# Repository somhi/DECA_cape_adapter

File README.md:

# DECA cape adapter

Working in a DECA cape adapter from [DECA retro cape 2](https://github.com/somhi/DECA_retro_cape_2) to a DE10-Lite FPGA board.

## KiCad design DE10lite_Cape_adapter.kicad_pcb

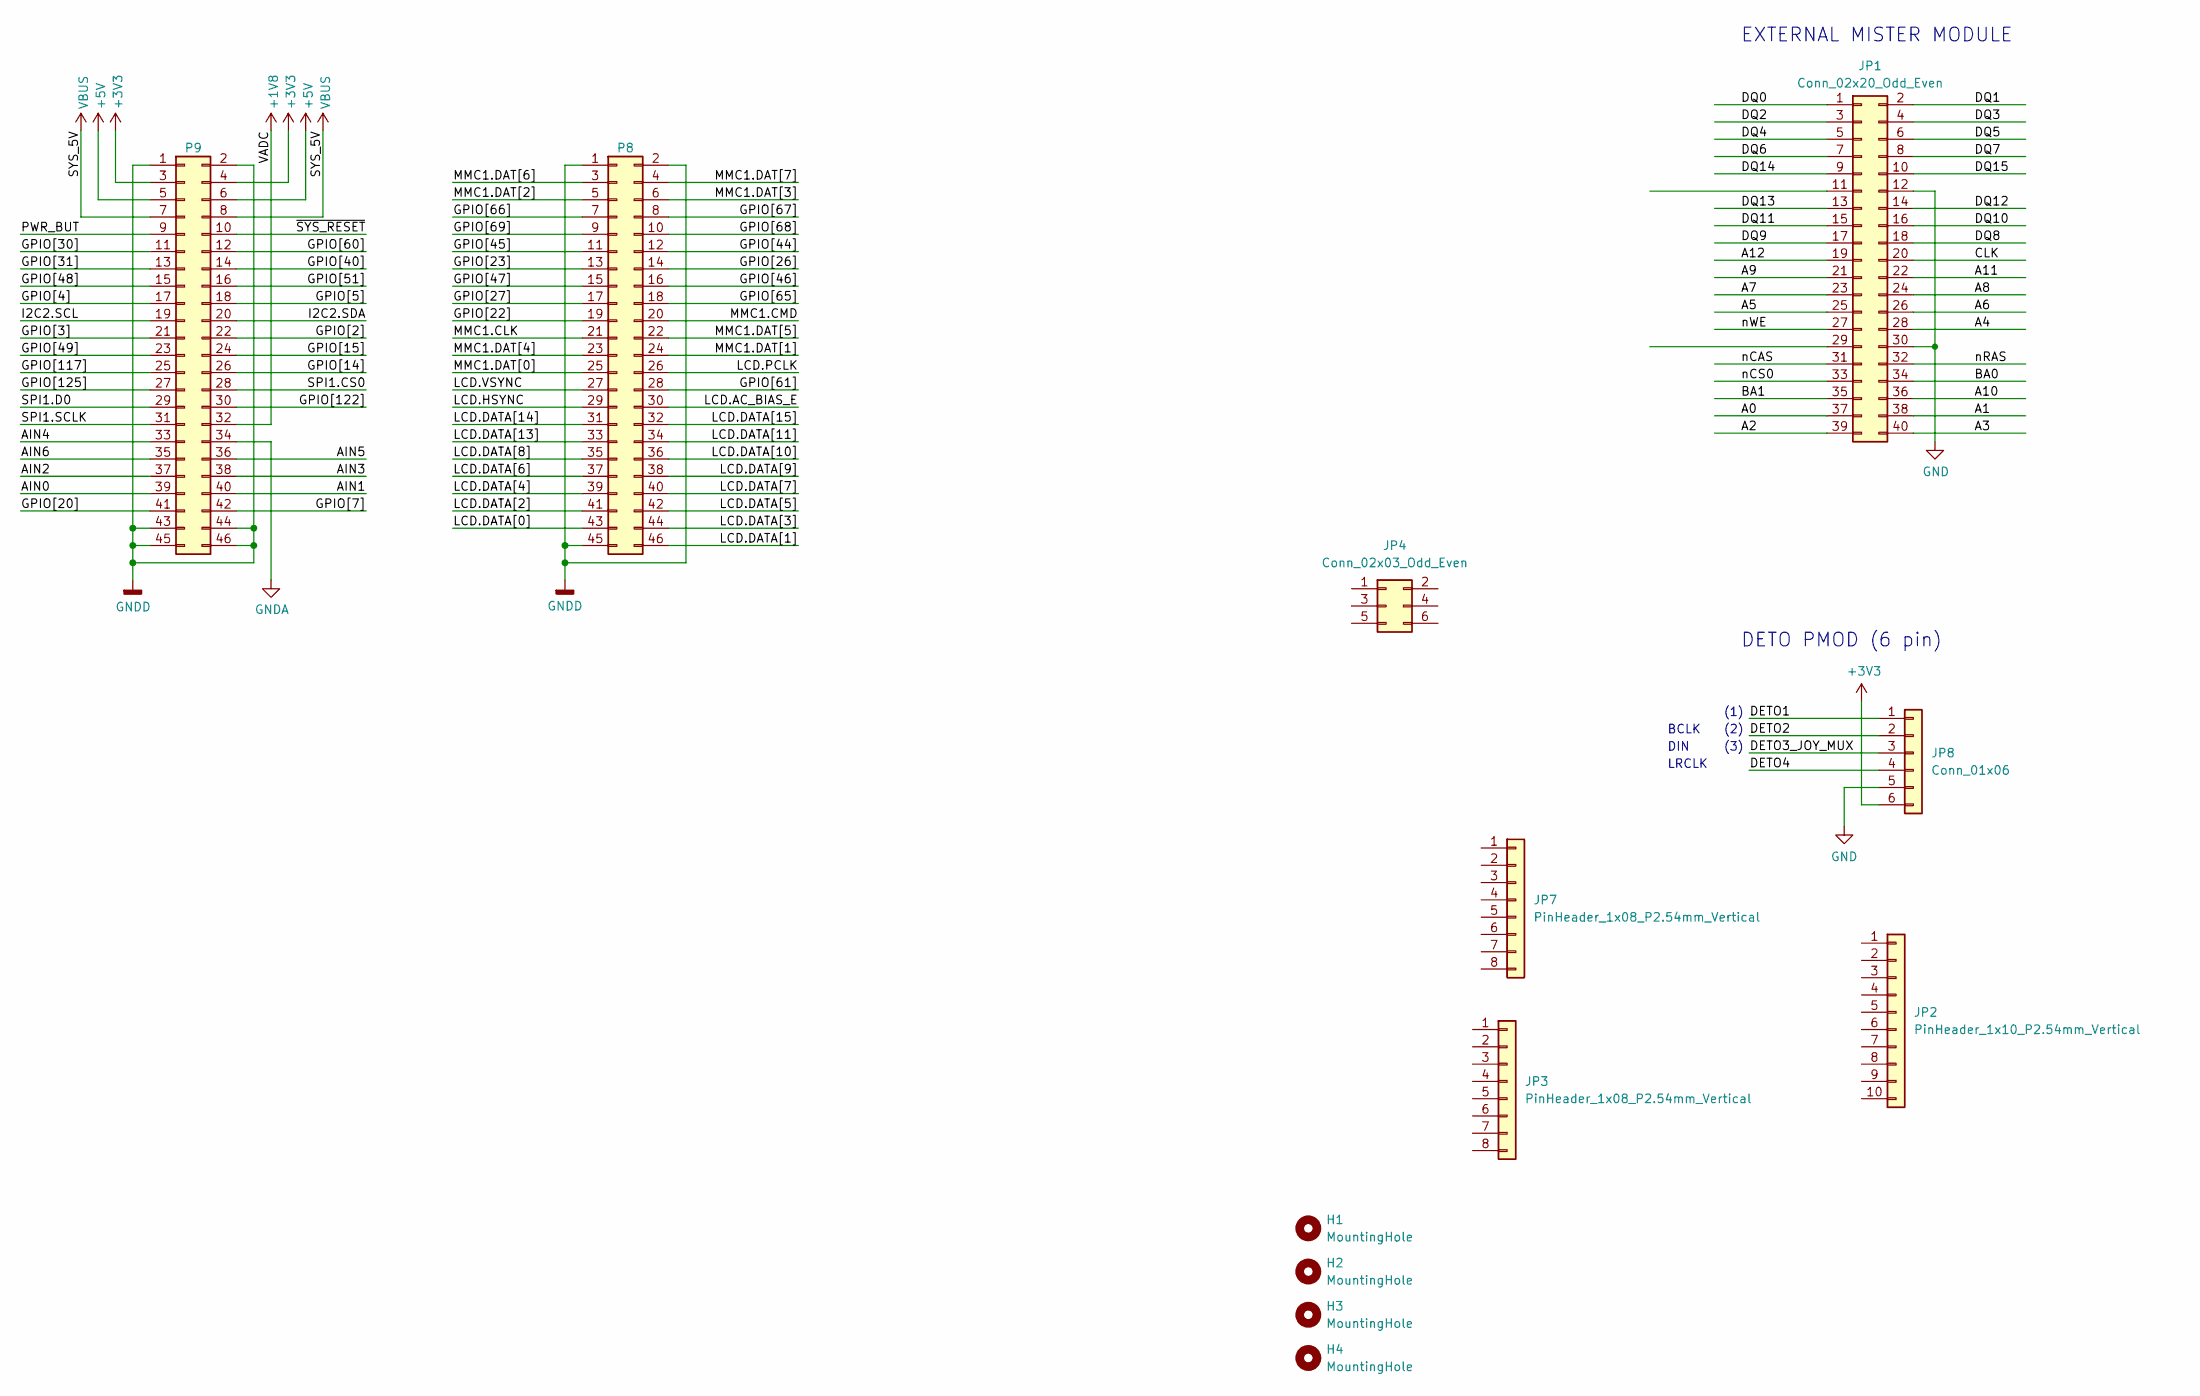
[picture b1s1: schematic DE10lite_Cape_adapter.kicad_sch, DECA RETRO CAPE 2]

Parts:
H1, H2, H3, H4: MountingHole; MountingHole_3mm
JP1: Conn_02x20_Odd_Even; PinSocket_2x20_P2.54mm_Vertical
JP2: PinHeader_1x10_P2.54mm_Vertical
JP3, JP7: PinHeader_1x08_P2.54mm_Vertical
JP4: Conn_02x03_Odd_Even; PinSocket_2x03_P2.54mm_Vertical
JP8: Conn_01x06; PinHeader_1x06_P2.54mm_Vertical
P8, P9: BeagleBone_Black_Header; PinHeader_2x23_P2.54mm_Vertical

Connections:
+1V8: P9.32
+3V3: JP8.6, P9.3, P9.4
+5V: P9.5, P9.6
/A0: JP1.37
/A1: JP1.38
/A2: JP1.39
/A3: JP1.40
/A4: JP1.28
/A5: JP1.25
/A6: JP1.26
/A7: JP1.23
/A8: JP1.24
/A9: JP1.21
/A10: JP1.36
/A11: JP1.22
/A12: JP1.19
/AIN0: P9.39
/AIN1: P9.40
/AIN2: P9.37
/AIN3: P9.38
/AIN4: P9.33
/AIN5: P9.36
/AIN6: P9.35
/BA0: JP1.34
/BA1: JP1.35
/CLK: JP1.20
/DETO1: JP8.1
/DETO2: JP8.2
/DETO3_JOY_MUX: JP8.3
/DETO4: JP8.4
/DQ0: JP1.1
/DQ1: JP1.2
/DQ2: JP1.3
/DQ3: JP1.4
/DQ4: JP1.5
/DQ5: JP1.6
/DQ6: JP1.7
/DQ7: JP1.8
/DQ8: JP1.18
/DQ9: JP1.17
/DQ10: JP1.16
/DQ11: JP1.15
/DQ12: JP1.14
/DQ13: JP1.13
/DQ14: JP1.9
/DQ15: JP1.10
/GPIO[2]: P9.22
/GPIO[3]: P9.21
/GPIO[4]: P9.17
/GPIO[5]: P9.18
/GPIO[7]: P9.42
/GPIO[14]: P9.26
/GPIO[15]: P9.24
/GPIO[20]: P9.41
/GPIO[22]: P8.19
/GPIO[23]: P8.13
/GPIO[26]: P8.14
/GPIO[27]: P8.17
/GPIO[30]: P9.11
/GPIO[31]: P9.13
/GPIO[40]: P9.14
/GPIO[44]: P8.12
/GPIO[45]: P8.11
/GPIO[46]: P8.16
/GPIO[47]: P8.15
/GPIO[48]: P9.15
/GPIO[49]: P9.23
/GPIO[51]: P9.16
/GPIO[60]: P9.12
/GPIO[61]: P8.28
/GPIO[65]: P8.18
/GPIO[66]: P8.7
/GPIO[67]: P8.8
/GPIO[68]: P8.10
/GPIO[69]: P8.9
/GPIO[117]: P9.25
/GPIO[122]: P9.30
/GPIO[125]: P9.27
/I2C2.SCL: P9.19
/I2C2.SDA: P9.20
/LCD.AC_BIAS_E: P8.30
/LCD.DATA[0]: P8.43
/LCD.DATA[1]: P8.46
/LCD.DATA[2]: P8.41
/LCD.DATA[3]: P8.44
/LCD.DATA[4]: P8.39
/LCD.DATA[5]: P8.42
/LCD.DATA[6]: P8.37
/LCD.DATA[7]: P8.40
/LCD.DATA[8]: P8.35
/LCD.DATA[9]: P8.38
/LCD.DATA[10]: P8.36
/LCD.DATA[11]: P8.34
/LCD.DATA[13]: P8.33
/LCD.DATA[14]: P8.31
/LCD.DATA[15]: P8.32
/LCD.HSYNC: P8.29
/LCD.PCLK: P8.26
/LCD.VSYNC: P8.27
/MMC1.CLK: P8.21
/MMC1.CMD: P8.20
/MMC1.DAT[0]: P8.25
/MMC1.DAT[1]: P8.24
/MMC1.DAT[2]: P8.5
/MMC1.DAT[3]: P8.6
/MMC1.DAT[4]: P8.23
/MMC1.DAT[5]: P8.22
/MMC1.DAT[6]: P8.3
/MMC1.DAT[7]: P8.4
/PWR_BUT: P9.9
/SPI1.CS0: P9.28
/SPI1.D0: P9.29
/SPI1.SCLK: P9.31
/nCAS: JP1.31
/nCS0: JP1.33
/nRAS: JP1.32
/nWE: JP1.27
/~SYS_RESET: P9.10
GND: JP1.12, JP1.30, JP8.5
GNDA: P9.34
GNDD: P8.1, P8.2, P8.45, P9.1, P9.2, P9.43, P9.44, P9.45, P9.46
VBUS: P9.7, P9.8

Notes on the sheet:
BCLK
DIN
LRCLK
(2)
(1)
DETO PMOD (6 pin)
EXTERNAL MISTER MODULE
(3)

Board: 2 copper layers, 15 parts (7 on the bottom side), 5 nets, no tracks yet.

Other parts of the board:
LO1: KiCad-Logo2_12mm_SilkScreen
LO2: OSHW-Logo2_14.6x12mm_SilkScreen
LO4: ESD-Logo_6.6x6mm_SilkScreen

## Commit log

2023-01-26 DE10-Lite connectors and outline
2023-01-26 added beaglebone headers
2023-01-26 updated filenames and added pinout

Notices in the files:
DE10lite_Cape_adapter.kicad_pcb:
License: CC-BY-SA v4.0
